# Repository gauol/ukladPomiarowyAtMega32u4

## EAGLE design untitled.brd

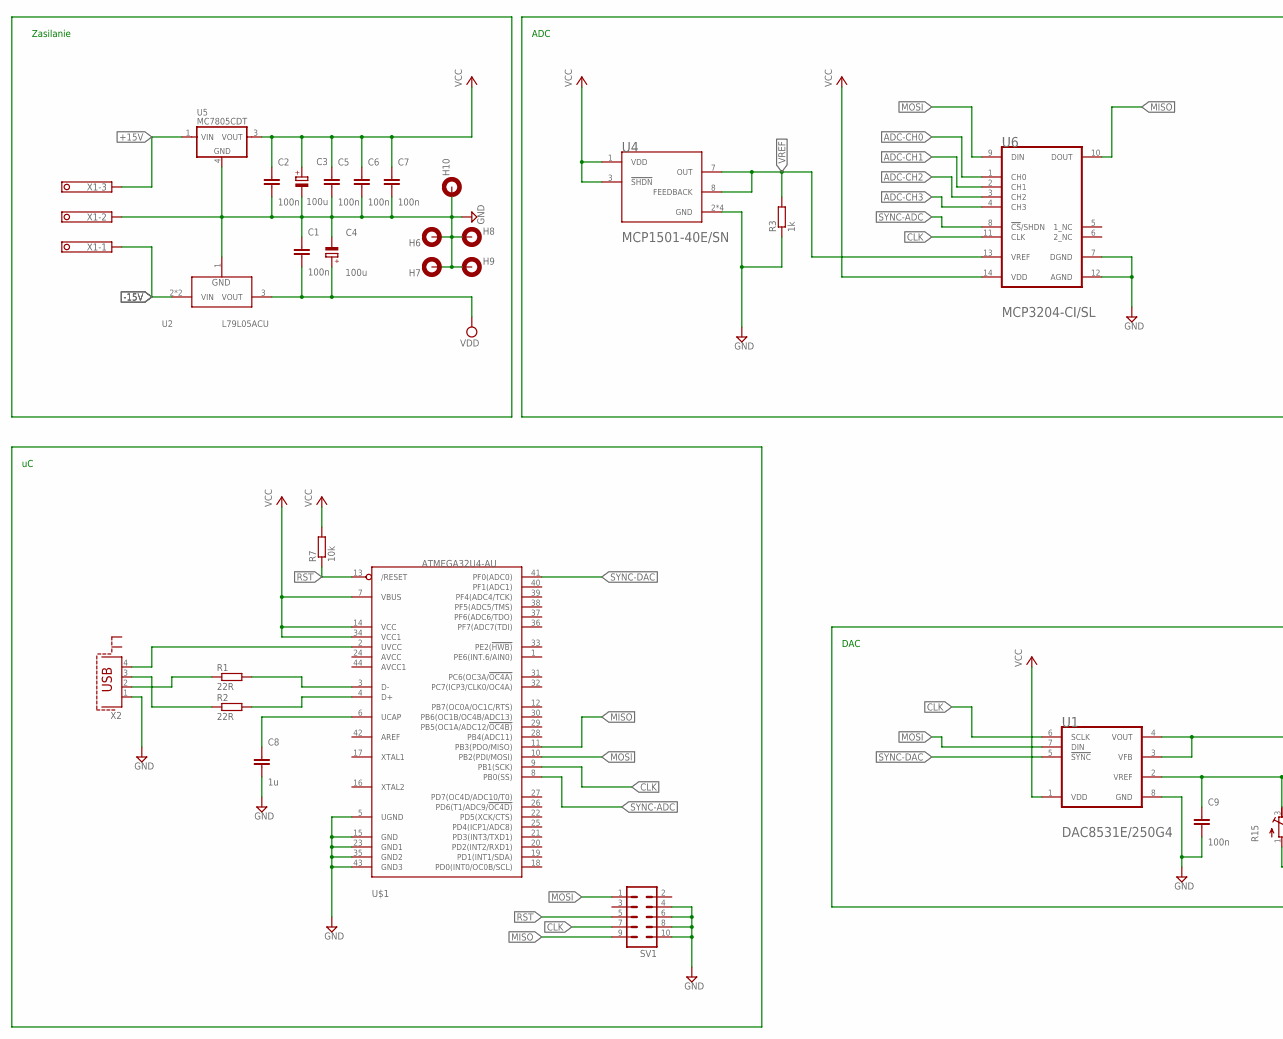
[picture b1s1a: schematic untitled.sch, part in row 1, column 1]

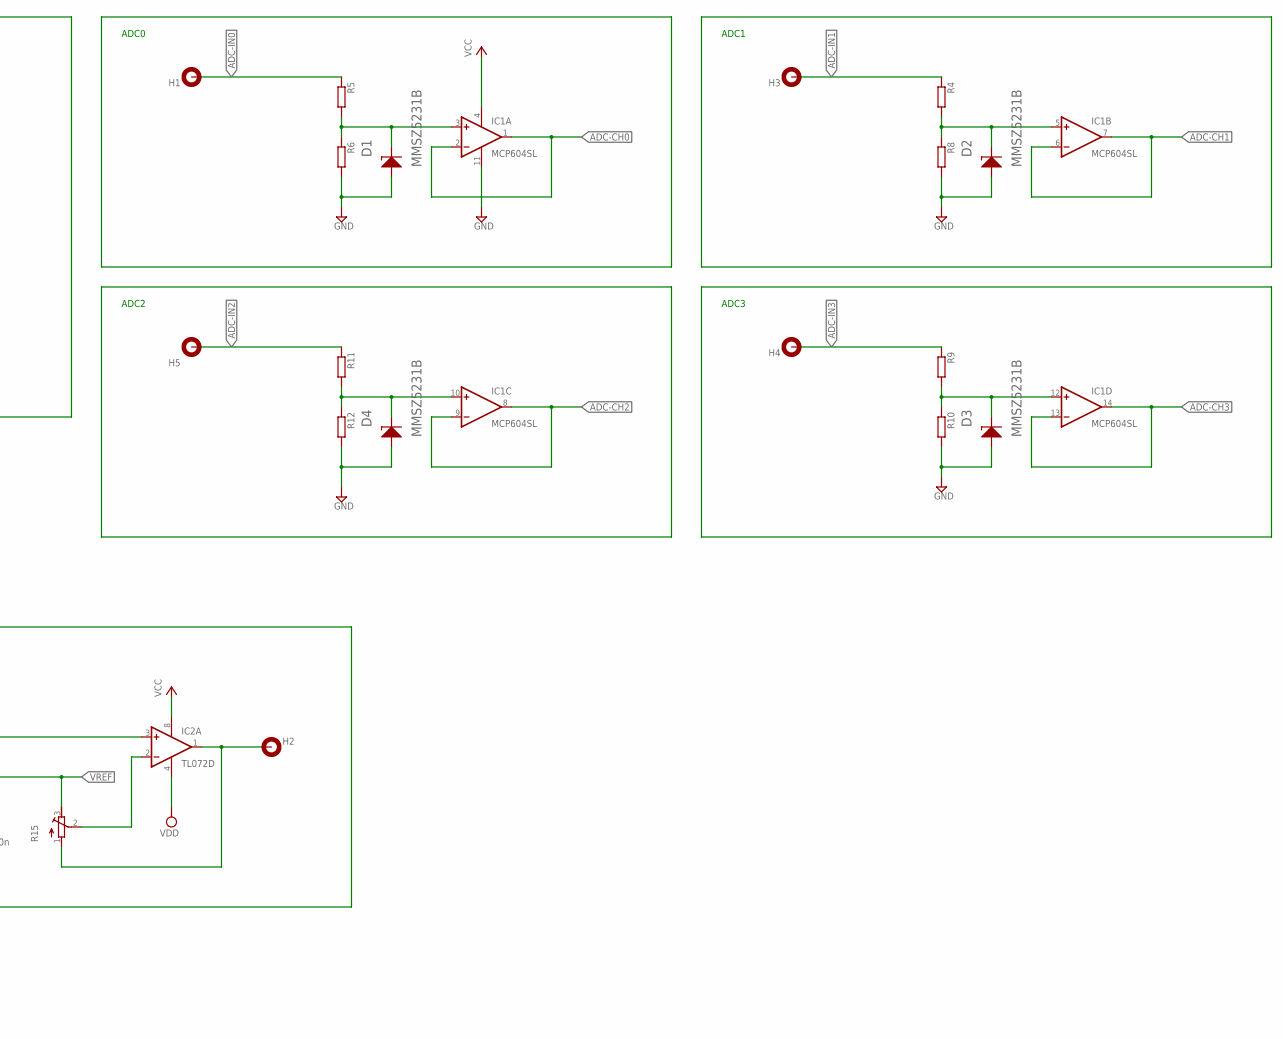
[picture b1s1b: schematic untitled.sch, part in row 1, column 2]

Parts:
C1, C2, C5, C6, C7, C9: 100n; C0805K
C3, C4: 100u; 153CLV-1014
C8: 1u; C0805K
D1, D2, D3, D4: MMSZ5231BVISHAY_SEMICONDUCTOR_MMSZ5231B-E3-08_0_0; VISHAY_SEMICONDUCTOR_MMSZ5231B-E3-08_0
H1, H2, H3, H4, H5, H6, H7, H8, H9, H10: MOUNT-PAD-ROUND2.8; 2,8-PAD
IC1: MCP604SL; SO14
IC2: TL072D; SO08
R1, R2: 22R; R1206
R3: 1k; M1206
R4, R5, R6, R8, R9, R10, R11, R12: R-EU_M1206; M1206
R7: 10k; M1206
R15: R-TRIMM64Y; RTRIM64Y
SV1: ML10
U1: TEXAS_INSTRUMENTS_DAC8531E-250G4TEXAS_INSTRUMENTS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; TEXAS_INSTRUMENTS_DAC8531E-250G4_0
U2: L79L05ACUTRL79L05ACU; L79L05ACUTR_1
U4: MCP1501-40E/SN; SOIC127P600X175-8N
U5: MC7805CDT; DPAK-3
U6: MCP3204-CI-SL; SO14
U$1: ATMEGA32U4-AU; TQFP44
X1: 1751251
X2: PN61729-S

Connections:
+15V: U5.1 (VIN), X1.3
-15V: U2.2 (VIN), U2.2-2 (VIN), X1.1
ADC-CH0: IC1.1 (OUT), IC1.2 (-IN), U6.1 (CH0)
ADC-CH1: IC1.6 (-IN), IC1.7 (OUT), U6.2 (CH1)
ADC-CH2: IC1.8 (OUT), IC1.9 (-IN), U6.3 (CH2)
ADC-CH3: IC1.13 (-IN), IC1.14 (OUT), U6.4 (CH3)
ADC-IN0: H1.B2,8, R5.1
ADC-IN1: H3.B2,8, R4.1
ADC-IN2: H5.B2,8, R11.1
ADC-IN3: H4.B2,8, R9.1
CLK: SV1.7, U1.6 (SCLK), U6.11 (CLK), U$1.9 (PB1(SCK))
GND: C1.1, C2.2, C3.-, C4.-, C5.2, C6.2, C7.2, C8.2, C9.2, D1.1 (A), D2.1 (A), D3.1 (A), D4.1 (A), H6.B2,8, H7.B2,8, H8.B2,8, H9.B2,8, H10.B2,8, IC1.11 (V-), R3.1, R6.2, R8.2, R10.2, R12.2, SV1.4, SV1.6, SV1.8, SV1.10, U1.8 (GND), U2.1 (GND), U4.2 (GND), U4.4 (GND), U4.5 (GND), U4.6 (GND), U5.4 (GND), U6.7 (DGND), U6.12 (AGND), U$1.5 (UGND), U$1.15 (GND), U$1.23 (GND1), U$1.35 (GND2), U$1.43 (GND3), X1.2, X2.1
MISO: SV1.9, U6.10 (DOUT), U$1.11 (PB3(PDO/MISO))
MOSI: SV1.1, U1.7 (DIN), U6.9 (DIN), U$1.10 (PB2(PDI/MOSI))
unnamed: R1.1, X2.2
unnamed: R1.2, U$1.3 (D-)
unnamed: R2.1, X2.3
unnamed: R2.2, U$1.4 (D+)
unnamed: H2.B2,8, IC2.1 (OUT), R15.1 (A)
unnamed: U$1.2 (UVCC), X2.4
unnamed: D2.2 (K), IC1.5 (+IN), R4.2, R8.1
unnamed: D1.2 (K), IC1.3 (+IN), R5.2, R6.1
unnamed: C8.1, U$1.6 (UCAP)
unnamed: D3.2 (K), IC1.12 (+IN), R9.2, R10.1
unnamed: IC2.3 (+IN), U1.3 (VFB), U1.4 (VOUT)
unnamed: D4.2 (K), IC1.10 (+IN), R11.2, R12.1
unnamed: IC2.2 (-IN), R15.2 (S)
RST: R7.1, SV1.5, U$1.13 (/RESET)
SYNC-ADC: U6.8 (!CS!/SHDN), U$1.8 (PB0(SS))
SYNC-DAC: U1.5 (!SYNC!), U$1.41 (PF0(ADC0))
VCC: C2.1, C3.+, C5.1, C6.1, C7.1, IC1.4 (V+), IC2.8 (V+), R7.2, U1.1 (VDD), U4.1 (VDD), U4.3 (!SHDN), U5.3 (VOUT), U6.14 (VDD), U$1.7 (VBUS), U$1.14 (VCC), U$1.34 (VCC1)
VDD: C1.2, C4.+, IC2.4 (V-), U2.3 (VOUT)
VREF: C9.1, R3.2, R15.3 (E), U1.2 (VREF), U4.7 (OUT), U4.8 (FEEDBACK), U6.13 (VREF)

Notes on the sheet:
Zasilanie
ADC
ADC0
DAC
ADC1
ADC3
ADC2

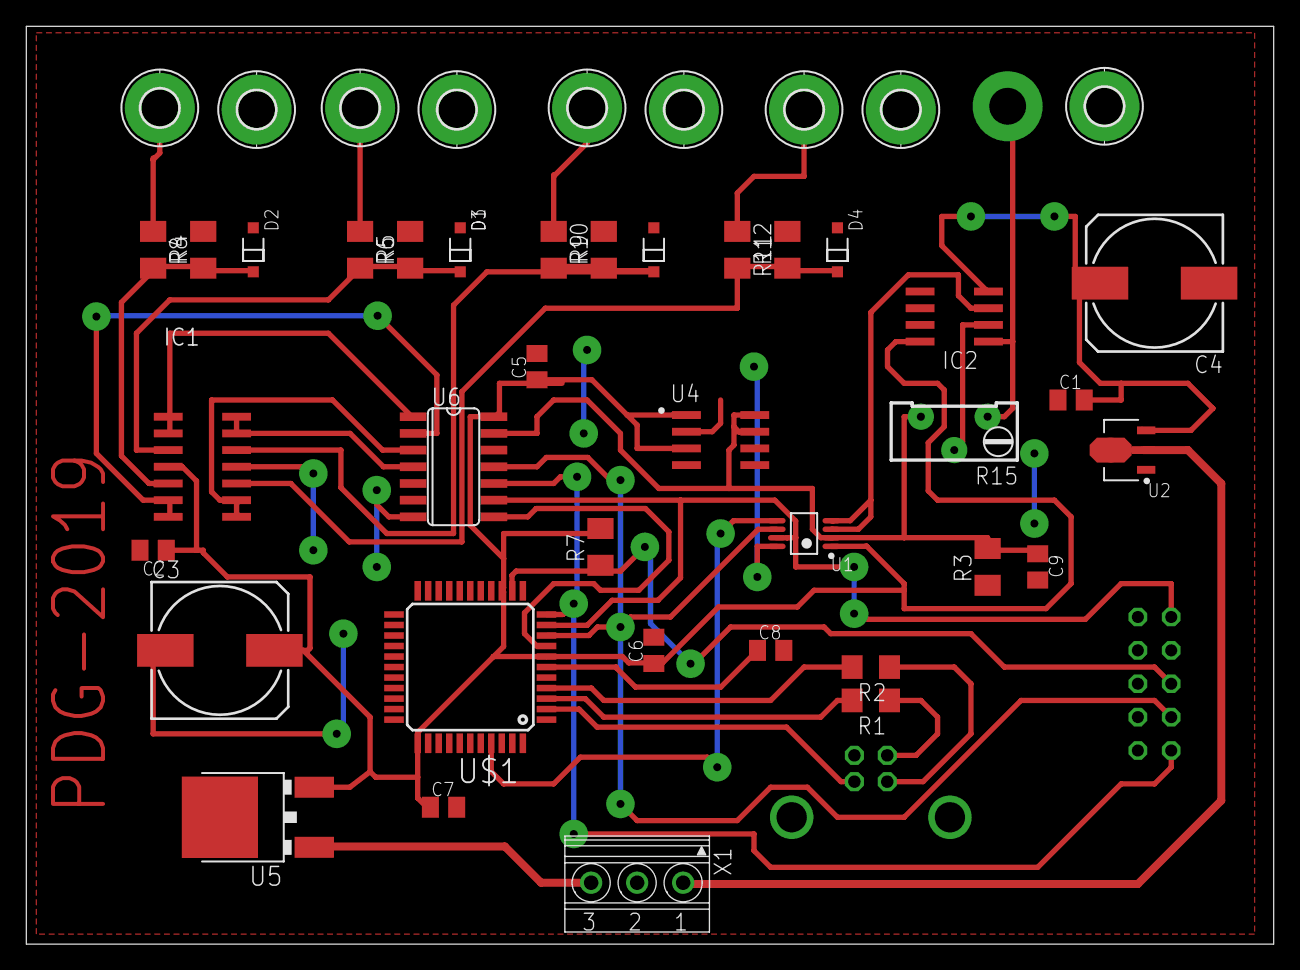
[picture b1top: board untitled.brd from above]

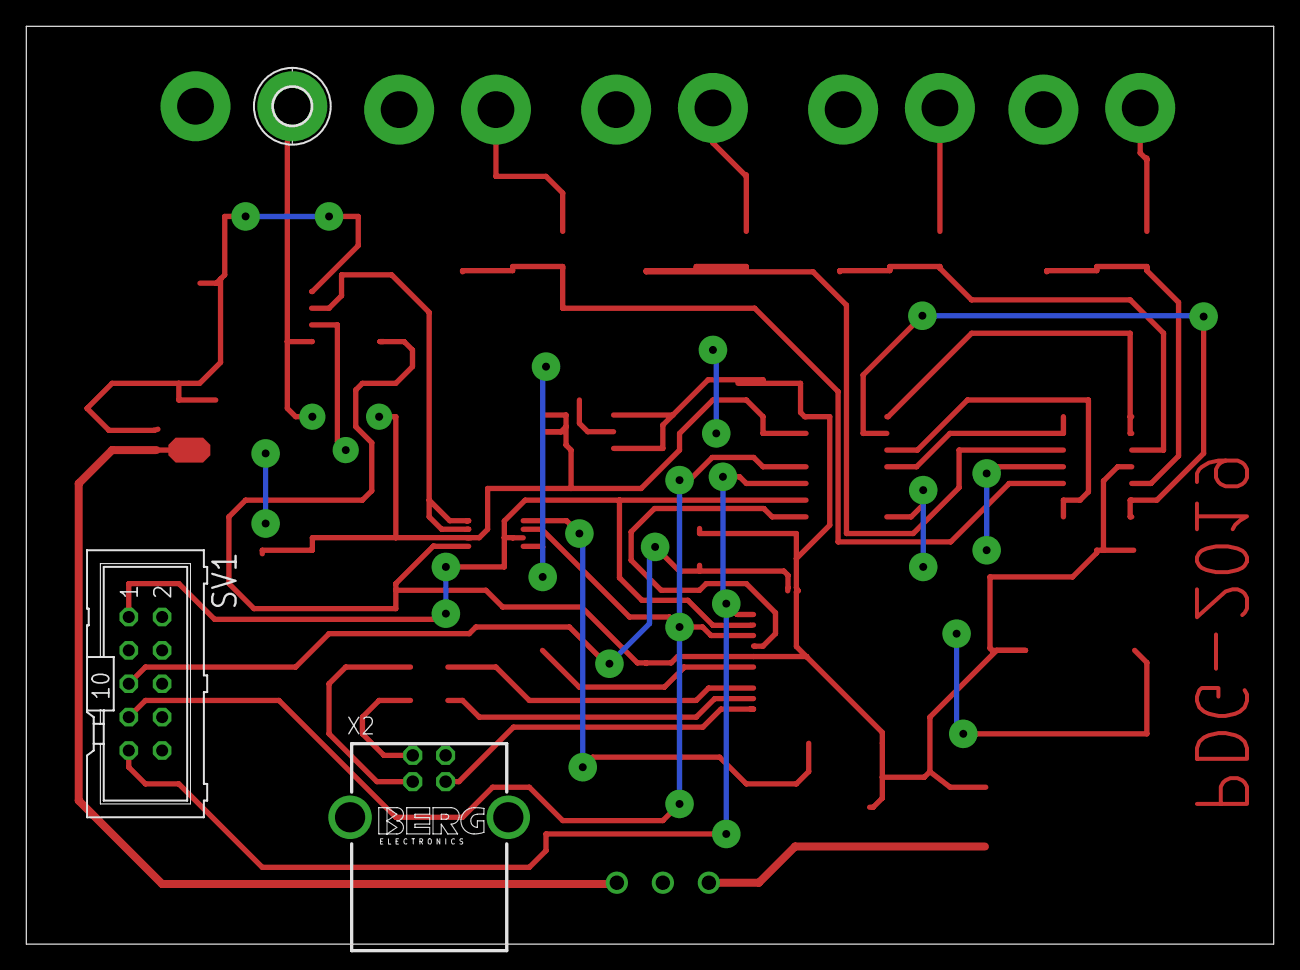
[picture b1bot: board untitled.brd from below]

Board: 2 copper layers, 94.9 x 69.8 mm, 47 parts (3 on the bottom side), 33 nets.

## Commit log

2019-04-20 dodano zlacze programatora i rezystor nastawny
2019-04-23 poprawki
